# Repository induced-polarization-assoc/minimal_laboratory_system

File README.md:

# minimal_laboratory_system
Signal generation, signal routing, testing harness, array designs, analog circuitry, data logging, and DSP hardware/firmware.

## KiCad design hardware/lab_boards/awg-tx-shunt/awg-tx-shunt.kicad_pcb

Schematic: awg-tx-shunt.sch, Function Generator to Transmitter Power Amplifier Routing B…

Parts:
C1, C2: 1uF C0G; C_1206_3216Metric_Pad1.42x1.75mm_HandSolder
E1: 1984659-phoenix-6pos-1984659; 1984659
H1, H2, H3, H4: MountingHole; MountingHole_3.2mm_M3_Pad_Via
J1, J2, J3, J4, J5: 1-1337543-0; CONN_1-1337543-0
L1, L2: T6003NL
R1: 100K; R_1206_3216Metric_Pad1.42x1.75mm_HandSolder
R2, R5, R6, R8: 1M; R_1206_3216Metric_Pad1.42x1.75mm_HandSolder
R3, R4, R10: WSL36373L000FEA (3mOhm); WSL36373L000FEA
R7, R9: 70R; R_1206_3216Metric_Pad1.42x1.75mm_HandSolder

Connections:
/HI_SHUNT_N: J5.2, L2.P$7, R9.1
/HI_SHUNT_P: J5.1, L2.P$9, R9.2
/INSHUNT_N: J2.2, R4.3
/INSHUNT_P: J2.1, R4.2
/LOW_SHUNT__ISO_N: J3.2, R10.3
/LOW_SHUNT__ISO_P: J3.1, R10.2
/POWERAMP_IN_N: E1.1, L1.P$7, R7.1, R8.2
/POWERAMP_IN_P: E1.2, R10.4
/POWERAMP_OUT_P: E1.6, R3.1
/TX1_IN: J1.1, R1.2
/TX1_OUT: J4.1, R3.4
/TX2_IN: J1.2, L1.P$4, R6.2
/TX2_OUT: E1.5, J4.2
/TXN-DIRECT: L1.P$7, R6.1
/TXN-IN: R2.4
/TXN-IN2: R2.1, R6.2
/TXN-ISO: L1.P$4, R6.3
/TXP-DIRECT: L1.P$9, R6.4
/TXP-IN: R6.5
/TXP-ISO: L1.P$2, R6.6
/TXSN-IN: R2.3
GNDPWR: J1.P1, J1.P2, J2.P1, J2.P2, R2.1, R6.1
GNDREF: E1.4, J5.P1, J5.P2, R8.1
GNDS: E1.3, J3.P1, J3.P2, J4.P1, J4.P2
unnamed: C1.2, R1.1
unnamed: C2.1, L2.P$2, R5.2
unnamed: C2.2, R3.2
unnamed: L1.P$2, R4.4
unnamed: L1.P$9, R7.2, R10.1
unnamed: L2.P$4, R3.3, R5.1

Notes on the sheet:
AWG IN
INPUT SHUNT
TX TO ARRAY
LOW SHUNT ISO
HIGH SHUNT
LOW SHUNT (ISOLATED)
TO POWER AMP
f_c = 1/2pi*R*C = 1/2*pi*1MOhm*1uF = 1/2pi = 0.32Hz
Floating High Shunt

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
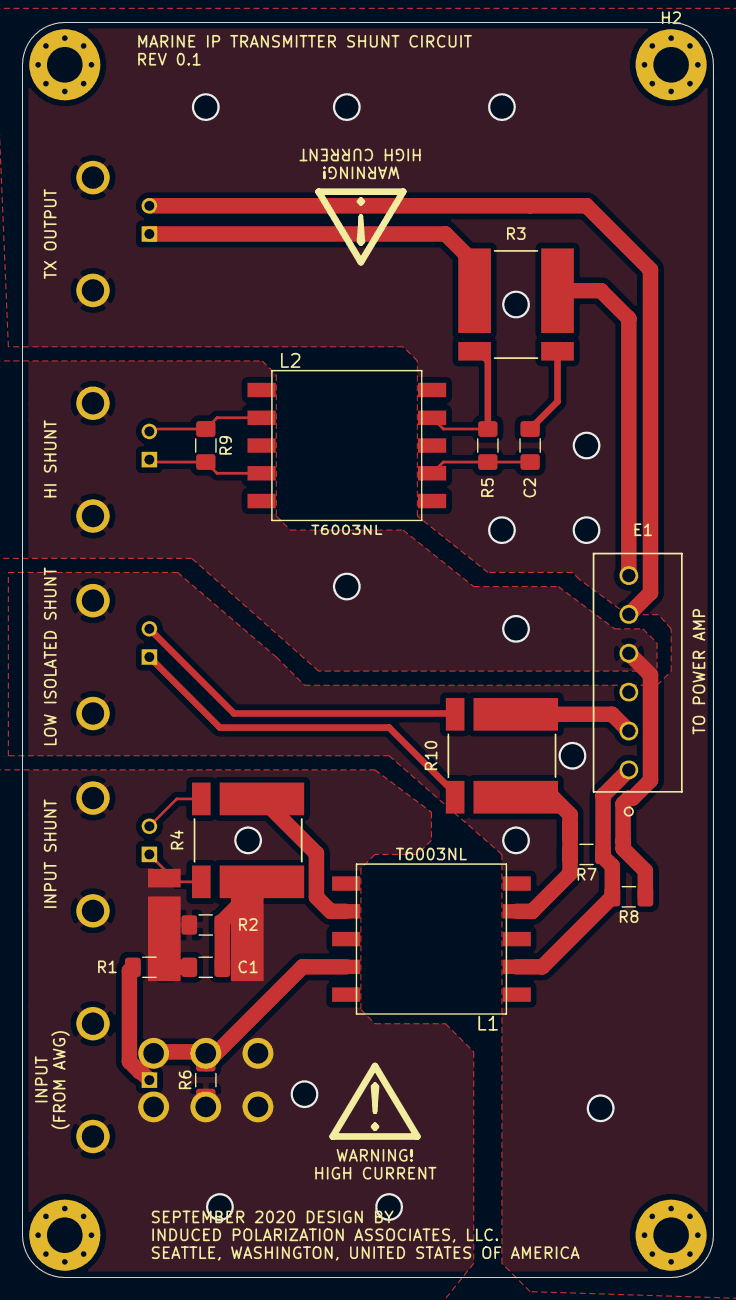
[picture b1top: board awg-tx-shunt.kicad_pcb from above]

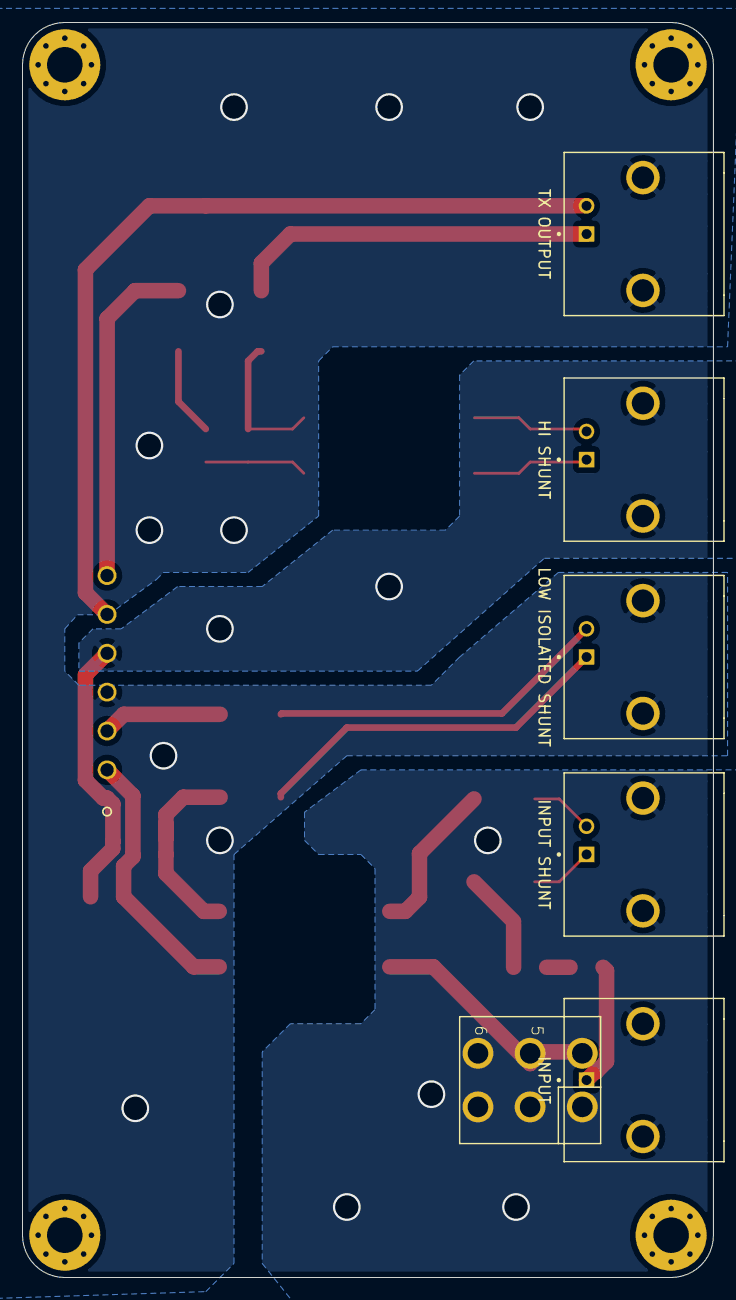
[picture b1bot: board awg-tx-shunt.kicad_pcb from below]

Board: 2 copper layers, 62.2 x 113.0 mm, 24 parts (5 on the bottom side), 28 nets.

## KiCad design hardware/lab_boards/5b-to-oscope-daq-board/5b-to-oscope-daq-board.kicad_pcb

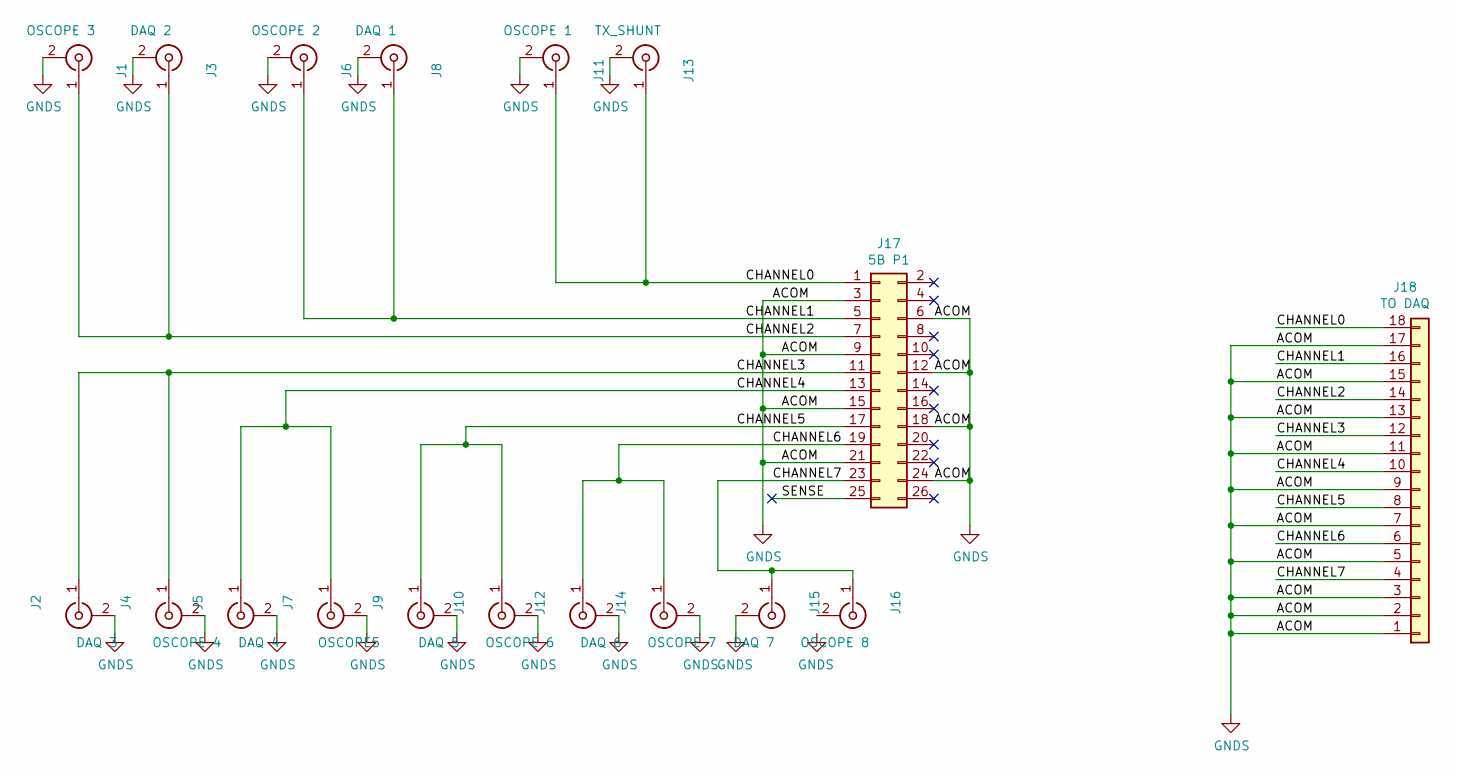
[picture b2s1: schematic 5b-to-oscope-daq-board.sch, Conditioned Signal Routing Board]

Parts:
J1: OSCOPE 3; BNC_Amphenol_B6252HB-NPP3G-50_Horizontal
J2: DAQ 3; BNC_Amphenol_B6252HB-NPP3G-50_Horizontal
J3: DAQ 2; BNC_Amphenol_B6252HB-NPP3G-50_Horizontal
J4: OSCOPE 4; BNC_Amphenol_B6252HB-NPP3G-50_Horizontal
J5: DAQ 4; BNC_Amphenol_B6252HB-NPP3G-50_Horizontal
J6: OSCOPE 2; BNC_Amphenol_B6252HB-NPP3G-50_Horizontal
J7: OSCOPE5; BNC_Amphenol_B6252HB-NPP3G-50_Horizontal
J8: DAQ 1; BNC_Amphenol_B6252HB-NPP3G-50_Horizontal
J9: DAQ 5; BNC_Amphenol_B6252HB-NPP3G-50_Horizontal
J10: OSCOPE 6; BNC_Amphenol_B6252HB-NPP3G-50_Horizontal
J11: OSCOPE 1; BNC_Amphenol_B6252HB-NPP3G-50_Horizontal
J12: DAQ 6; BNC_Amphenol_B6252HB-NPP3G-50_Horizontal
J13: TX_SHUNT; BNC_Amphenol_B6252HB-NPP3G-50_Horizontal
J14: OSCOPE 7; BNC_Amphenol_B6252HB-NPP3G-50_Horizontal
J15: DAQ 7; BNC_Amphenol_B6252HB-NPP3G-50_Horizontal
J16: OSCOPE 8; BNC_Amphenol_B6252HB-NPP3G-50_Horizontal
J17: 5B P1; IDC-Header_2x13_P2.54mm_Vertical
J18: TO DAQ; PinHeader_1x18_P2.54mm_Vertical

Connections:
/CHANNEL0: J11.1 (In), J13.1 (In), J17.1, J18.18
/CHANNEL1: J6.1 (In), J8.1 (In), J17.5, J18.16
/CHANNEL2: J1.1 (In), J3.1 (In), J17.7, J18.14
/CHANNEL3: J2.1 (In), J4.1 (In), J17.11, J18.12
/CHANNEL4: J5.1 (In), J7.1 (In), J17.13, J18.10
/CHANNEL5: J9.1 (In), J10.1 (In), J17.17, J18.8
/CHANNEL6: J12.1 (In), J14.1 (In), J17.19, J18.6
/CHANNEL7: J15.1 (In), J16.1 (In), J17.23, J18.4
/SENSE: J17.25
GNDS: J1.2 (Ext), J2.2 (Ext), J3.2 (Ext), J4.2 (Ext), J5.2 (Ext), J6.2 (Ext), J7.2 (Ext), J8.2 (Ext), J9.2 (Ext), J10.2 (Ext), J11.2 (Ext), J12.2 (Ext), J13.2 (Ext), J14.2 (Ext), J15.2 (Ext), J17.3, J17.6, J17.9, J17.12, J17.15, J17.18, J17.21, J17.24, J18.1, J18.2, J18.3, J18.5, J18.7, J18.9, J18.11, J18.13, J18.15, J18.17

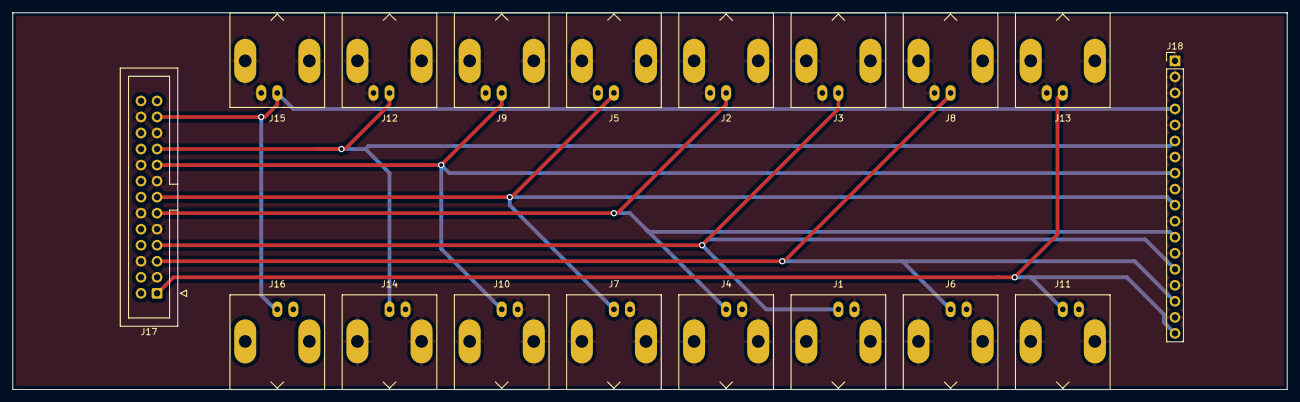
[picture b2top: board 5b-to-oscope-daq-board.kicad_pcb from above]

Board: 2 copper layers, 201.9 x 59.7 mm, 18 parts (0 on the bottom side), 9 nets.

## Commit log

2020-03-19 First Commit.
2020-03-19 Added skeletal structure for hardware repo.
2020-03-20 Added an overview/block diagrams directory and README.md.
2020-09-02 Added ipa-lab-setup-2020.drawio
2020-09-03 added .gitignore to local repo.
2020-09-03 Added design for lab routing board for signals between 5B amps module, oscilloscope, and data logger.
2020-09-03 Added an AWG to TX array connection and calibration board project
2020-09-03 Added T6003NLT symbol and footprint to awg-tx-shunt.sch to replace the generic transformer originally placed.
2020-09-04 added shunt resistor footprint.
2020-09-12 Reworked the TX routing board and transformer PCB layout. Simplified by removing calibration circuitry, which will be in a separate board design. Added test points.
2020-09-14 Revisions to awg-shunt-tx.sch shunt resistor.
2020-09-14 Added identifier text, warning symbols, and chamfered edges to the edge cuts, and rerouted wiring under the BNC connectors.
2020-09-14 Ran DRC. No errors.
2020-09-14 Added fabrication output files and reports in ROOT/awg-tx-shunt/to_fab_house_plots/
2020-09-14 Added pdf plots of the AWG to TX/shunt board.
2020-09-16 Added power amp schematic project
2020-09-16 Added some changes to the awg-tx-cal-box.pro
2020-09-17 Added some images of the schematics and a compressed file for sending to fabrication house.
2020-09-17 Added two DPDT switches to the board and rerouted to avoid using the bottom layer grounding plane.
2020-09-21 Added some notes to the shunt board design.
2020-09-22 Reworked the isolation and grounding scheme, added two shunt resistors and two connectors for each.
2020-09-22 reworked the whole board so the grounds are properly isolated and can be connected to a common star ground offboard. No vias are necessary for routing, either, which is a good thing for signal integr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
2020-09-22 added fabrication plots and compressed.
2020-09-23 Added some images/documents of the board schematics, layout, etc.
2020-10-15 Modifications to shunt placement.
2020-10-20 Totally rearranged the project to reflect new design requirements.
2020-10-20 Added some TTL logic controls for interfacing with either the USB DAQ or a custom MCU solution.
2020-10-29 Removed unnecessary/nonfunctional components from TX AWG Shunt board. Added OPA547 to integrate the power amplification into the design. Added output protection and Zobel network for load stabilizati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

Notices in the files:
parts and their libraries:
Copyright 2016 Accelerated Designs. All rights reserved.
